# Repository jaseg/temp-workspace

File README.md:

# Speed of the yanartas-sensors sampling front end, with and without the redriver

ngspice simulation of one channel of the sampling front end on the sensing board
(`sensing/yanartas-pillowbox-sensing.kicad_sch` in yanartas-sensors, commit `b0547da`).
Written by an LLM (Claude); nothing in yanartas-sensors was changed.

Two topologies are compared:

- **Redriver as drawn**: FPGA pin → 10 Ω → 220 nF → U2 (PI3HDX12311) → 220 nF → splitter / clip lines.
- **No redriver**: U2 not fitted and each RX pad linked to its TX pad, so the FPGA pin
  drives the splitter and the strobe clip lines itself. Simulated with VCCIO1 at 1.2 V
  (R54, as fitted) and at 3.3 V (the R55 option).

## Result

The speed of the sampler is set by the strobe pulse, and the strobe pulse is set by the
edge that reaches the clip lines. The clip lines are 13.3 mm long (about 160 ps there
and back). An edge slower than that gives a pulse that is as wide as the edge and lower.

| | Sampler 10–90 % rise time (bandwidth) at FPGA edge 150 / 300 / 600 ps | Stimulus 10–90 % at the TDR port |
|---|---|---|
| Redriver, limiting | 134 / 133 / 134 ps (2.6 GHz) | 185 / 228 / 241 ps |
| Redriver, linear | 167 / 236 / 488 ps (2.1 / 1.5 / 0.7 GHz) | 295 / 401 / 689 ps |
| No redriver, 1.2 V | 156 / 283 / 656 ps (2.2 / 1.2 / 0.5 GHz) | 324 / 471 / 819 ps |
| No redriver, 3.3 V | 103 / 82 / 390 ps (at bias +0.93 / +0.53 / +0.20 V per rail) | 326 / 421 / 791 ps |

- **The redriver only makes the front end faster if it limits.** A limiting redriver
  regenerates the edge, so the sampler is about 135 ps whatever the FPGA does. A linear
  redriver passes the FPGA edge on, and the front end is then 10 to 25 % faster than
  without it at 300 to 600 ps FPGA edges and no faster at 150 ps.
- **Which of the two the PI3HDX12311 does on this board is not known.** The part is
  linear for HDMI 2.x and limiting for HDMI 1.4, selected by its straps and its DDC
  listener. I could not obtain the full datasheet (DS46192), so both are simulated.
- **The FPGA edge rate is not known either.** Gowin publishes no slew rate or IBIS data
  for the GW1NZ-1, so it is swept from 150 to 600 ps (20–80 %).
- **Without the redriver at 3.3 V** the strobe pulse is 1.1 to 2.5 V, which allows a
  real reverse bias, so only the tip of the pulse turns the bridge on. That gives the
  fastest sampler of the four cases at FPGA edges up to 300 ps. The stimulus, however,
  would then reach the bridge with 4.3 V differential (the BAT15 is rated 4 V reverse),
  so the stimulus should stay on the redriver. The next section does that.

## Optimised operating point

Free choice of VCCIO1 and of whether the strobe passes through U2; the stimulus stays
on U2. For each option the bridge bias was swept (`sim/optimize.py`,
[all results](results/optimize.md)).

**Recommendation: VCCIO1 at 3.3 V, strobe bypassing U2, bias about +0.45 V per rail**
(VBIAS_K − VBIAS_A ≈ 0.9 V).

| FPGA edge | Operating point | Sampler 10–90 % | Gain | Efficiency | Overshoot |
|---|---|---|---|---|---|
| 150 ps | bypass, 3.3 V, bias +0.55 V | 99 ps | 0.27 | 24 % | 17 % |
| 300 ps | bypass, 3.3 V, bias +0.45 V | 123 ps | 0.25 | 17 % | not recorded |
| 300 ps | bypass, 3.3 V, bias +0.40 V | 152 ps | 0.30 | 23 % | 7 % |
| 600 ps | bypass, 3.3 V, bias +0.30 V | 187 ps | 0.12 | 7 % | 13 % |
| any | through U2 if it limits, bias 0 V | 141–142 ps | 0.15 | 9–10 % | 20–30 % |
| 300 ps | as drawn: through U2 linear, 1.2 V, bias −0.13 V | 236 ps | 0.14 | 16 % | not recorded |

- **Why it is better.** The bias is the speed control: raising it shortens the part of
  the pulse that turns the bridge on, at the price of efficiency. Only a large strobe
  leaves room to do that. Through U2 the pulse is 0.75 V at most and the bridge stops
  working above about 0.1 V of bias.
- **Reverse bias at last.** At +0.45 V per rail the diodes stay off for the ±0.26 V
  that the stimulus puts on the bridge. In the TDR trace the baseline before the edge
  is flat, where the as-drawn case sloped.
- **Recorded TDR edge** (FPGA edge 300 ps): 294 ps incident with U2 linear in the
  stimulus path, against 493 ps as drawn. With U2 limiting the reflected edge is 133 ps.
- **When not to bypass.** At a 600 ps FPGA edge the bypassed strobe needs a low bias and
  is slower than a limiting U2 (187 ps against 141 ps). If the FPGA turns out that slow
  and U2 limits, keep the strobe on U2.
- **VCCIO 2.5 V** is nearly as good (119 ps at +0.30 V and 300 ps, 10 % efficiency) if
  3.3 V is a problem for the other pins of that bank.

What limits the recorded incident edge at this operating point (FPGA edge 300 ps):

| Stimulus path | Edge at the bridge input, 10–90 % | Sampler alone | Limit |
|---|---|---|---|
| U2 linear | 398 ps (409 ps at the FPGA pin) | 122–155 ps | The FPGA edge; U2 passes it on unchanged |
| U2 limiting | 92 ps | 122–155 ps | The sampler for the main rise (about 150 ps in the trace), then a dip 200 ps after the edge |

- The 294 ps read from the trace with U2 linear is shorter than the stimulus itself and
  is not a faithful figure. With the open test line the stimulus rests at ±0.47 V per
  side, as large as the 0.45 V bias, so the bridge compresses the lower end of the edge.
  The ±0.26 V quoted above only holds for a terminated line. For an open or high-impedance
  load the stimulus has to be smaller or the bias larger.
- The sampler slows from 122 ps to 155 ps as the input step grows from 0.05 V to 0.52 V
  per side, and its efficiency falls from 20 % to 11 %.
- The dip with U2 limiting is a reflection from U10, 16.4 mm from the splitter. U10 is
  modelled as 8 Ω with 0.5 pF on each side, which is an estimate, so the size of the dip
  is uncertain. It turns the 10–90 % reading into 345 ps.

Changes on the board:

| Change | Why |
|---|---|
| Fit R55 instead of R54 | VCCIO1 = 3.3 V |
| R78, R79, R82, R83: 10 Ω → about 220 Ω | The stimulus pins now swing 3.3 V; this keeps U2's input near 1.2 V differential. Value not optimised |
| Strobe: connect STROBE_R to STROBE_C through one 220 nF, leaving U2 channels B and D unconnected | Bypass. In the model this is a 1 nH link across the U2 pads; a wire bodge will differ |
| Bias: VBIAS_K ≈ 2.1 V, VBIAS_A ≈ 1.2 V | Tune per board: sweep the bias and take the fastest edge that still has enough amplitude |

Diode reverse voltage at this operating point, simulated over both strobe edges with
the stimulus on an open line (BAT15-04W rating: 4 V): 1.70 V worst case at a 300 ps
FPGA edge, 1.91 V at 150 ps, and 2.17 V at 150 ps with the bias raised to 0.70 V. The
peak falls on the non-sampling strobe edge.

Not checked: the other pins of bank 1 at 3.3 V, the FPGA's drive into the 10 Ω strobe
series resistors at 3.3 V, and R3–R6 (91 Ω), which were left as they are.

In the recorded TDR trace of the four original cases (FPGA edge 300 ps), the incident
edge takes 493 ps with the linear redriver and 541 ps without it at 1.2 V. The
no-redriver 3.3 V trace is left out of that figure. The trace with the limiting redriver is
too noisy to measure, because only 4 % of the error is removed per strobe there.
All numbers are in [results/summary.md](results/summary.md).

## Other things the simulation shows

These apply to both topologies and matter more than the redriver question.

1. **The strobe is barely large enough to turn the bridges on.** With the redriver the
   pulse between the clip-line nodes is 0.2 to 0.75 V, against two diode drops plus
   2 × 91 Ω. To get a 0.65 V forward peak, VBIAS_K − VBIAS_A has to be between +0.1 V
   and −0.4 V, that is, zero or forward bias at idle. The sampling efficiency is then 4
   to 20 % per strobe.
2. **The held voltage is only 0.1 to 0.2 of the input.** Each bridge rail is fed
   through 91 Ω from a clip-line node that is AC-grounded by C73/C74, so the rails are
   not floating. While the bridge conducts, the hold node settles to a divider between
   the signal and the rails.
3. **The stimulus is larger than the bias.** It arrives at the bridge with 0.9 to
   1.4 V differential, so the diodes conduct between strobes. This shows as the sloping
   baseline before the first edge in the TDR trace.

## Method

- `tools/kinet.py` and `tools/pcbpaths.py` read the netlist and the pad-to-pad trace
  lengths from the KiCad files (the files are from a KiCad nightly that no packaged
  `kicad-cli` reads). Their output is in `extracted/`.
- `sim/frontend.py` builds the ngspice deck: both halves of channel 1, traces as LC
  ladders (50 Ω, 6.05 ps/mm), 0402 capacitors with 0.4 nH, the two bridges with their
  91 Ω feeds, hold capacitor and the trace to U13.
- The sampler is measured in equivalent time. For each strobe delay, two transients
  with different starting hold voltages give the voltage a repetitive strobe converges
  to, and the fraction of the error removed per strobe.
- "Sampler rise time" is that held voltage against delay for a 1 ps step driven into
  SPL_HS from 50 Ω. The bias is set per case so that the strobe peaks 0.65 V forward
  across a bridge. With the limiting redriver the response overshoots by 60 % for
  about 300 ps, so its 10–90 % figure flatters it.
- `sim/experiments.py` runs everything (about 40 minutes on 4 cores, ngspice 42),
  `sim/plots.py` makes the figures and the table.

## Assumptions

| Item | Value | Basis |
|---|---|---|
| BAT15-04W | Infineon chip model D315 v7.0, plus 0.7 nH and 0.16 pF per diode | model file; package values from datasheet LS 1.4 nH and C 0.3 pF |
| FPGA output | ramp 150 / 300 / 600 ps into 30 Ω (1.2 V) or 12 Ω (3.3 V), 3 pF | estimate from the DC drive spec; no edge data published |
| PI3HDX12311 | 50 Ω in and out, 9 GHz, 80 ps delay, 1 Vpp differential swing. Linear: 0 dB with 5.6 dB peaking at 6 GHz. Limiting: 20 dB into the same clamp | estimate from the product brief; full datasheet not read |
| Redriver passes single edges at low repetition rate | assumed | not confirmed; a signal-detect or squelch would break this |
| U10 TMUXHS4212 | 8 Ω with 0.5 pF each side | estimate |
| Mesh | ideal 50 Ω line, 1 ns, open | U4/U12, U3/U9, connectors and the mesh itself are not modelled |
| Traces | lossless | |
| Leakage of the hold node between strobes | ignored | |

The estimates decide the absolute numbers. The comparison between the cases depends
mainly on the two unknowns named above.

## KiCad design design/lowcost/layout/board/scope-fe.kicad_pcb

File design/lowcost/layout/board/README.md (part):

# layout/board: scope-fe integrated board (six layers), as built 25 Nov 2026 (BOM-2)

One full run of `python3 gen_board.py` (about 115 s; `--prepower` stops before the supplies, `--powonly` after them; `--fast`
is still broken) builds `scope-fe.kicad_pcb` / `.kicad_pro` / `routes.json`. Renders: `python3 render_board.py` (boardlib `render`, refilled
copy): `scope-fe-L1.png` ... `L6`, `scope-fe-all.png`, `scope-fe-detail-{analog,fpga-south,mcu,power}.png`.

## BOM-2 repair, 25 Nov 2026 (SPEC decision 35, re-check `docs/validation/recheck-bom2.md`)
Full `gen_board.py` run after two block changes; outline, block positions and interfaces unchanged.
- **analog:** R106 is 10 M 0603 now, on B.Cu at (7.50, 15.90) board (block-local 7.50 / 14.90), horizontal. R105.2 ->
  0.3 mm top track (down, 45 degrees west) -> via (6.675, 14.95) -> R106.1; IN_BIAS comes down x 8.52 on B.Cu and jogs
  onto R106.2 (the old IN_BIAS via at x 7.0 is gone). Via hole edge 0.37 mm from the R106 pad; 0.33 mm from R106.2
  to the -5V B track. The top-side 0402 column R105 / (empty) / C107 is unchanged otherwise.
- **phase:** silkscreen within 0.3 mm of the west board edge goes to F.Fab (`silk_fix`): D319's clipped outline.
- **Checks:** check_board 0 missing, extra 4 (H1-H4), 0 footprint / value / pad-net, 0 unrouted, 0 clearance, 0 corner,
  0 off-axis, 0 RF width / gap, 0 courtyard, 0 unconnected (486 footprints, 3475 tracks, 1019 vias); fast-net segments on
  L3 0; 370 L1 / L6 samples without L2 / L5, all antipads or listed windows; L4 +3V3 one polygon; via_in_pad FAIL 0
  (23 near, 31 EP-allowed); DRC jlc4 + parity **0 errors, 0 unconnected, 450 warnings** (the D319 silk_edge_clearance
  is gone); decap_audit 77 capacitors, D1 1, D2s 8, D2g 1, D2p 10 (unchanged). Renders regenerated and looked at
  (L1-L6, all, detail-analog; net views of the R106 area on F and B).
- **Correction (re-check B2-10):** the +2V5 column feed (0.25 mm over 15 mm on L3) carries the trigger selector
  (12.3 mA in signal mode) plus the TLV3801 (up to 26.6 mA), about 40 mA, not "a few mA"; drop about 5 mV, TLV3801
  VCC-GND still >= 2.44 V. Q301 / Q302 emitters are 6-7 mm from the nearest +/-2V5 capacitor (static switch).

## As built 25 Nov 2026 (BOM-2 integration)
All six blocks were regenerated against the BOM-2 netlist, and the board was rebuilt with a full `gen_board.py` run.
The outline is unchanged (100.0 x 57.0 mm), and so are every block position and every interface.

**Front column fix.** The new diode-bridge switch first left the phase column's +2V5 / -2V5 vias unreachable by the
rail router (5 islands failed). Changes (TOPOLOGY.md section 11):
- **TRIG_SEL:** L3 via at (11.3, 23.85), then a 4.3 mm L6 piece to R386. The block's full-height L6 lane is removed.
- **DAC_TRIG:** swaps places with TRIG_SEL in the slow bundle. It is grid-routed east of a fence and enters only
  the column's south end.
- **-2V5:** L6 along x 9.4 (11.2 mm) and an L3 link (4.0 mm).
- **+2V5:** L3 from the Q301 via down the x 9.85 lane (15.9 mm) and to U302's via (10.6 mm). `widen()` grows these
  where room allows.
- **Phase block:** SW_SB now branches south of the U302 +2V5 via (gen_phase.py).

Slow lines: DAC_TRIG 92.5 mm, TRIG_SEL 81.6 mm (incl. the L6 piece 4.3).
Rails: +2V5 is 202 mm on L3 and 33 mm on L6, narrowest 0.25 mm over 15 mm (the explicit column feed, about 40 mA: selector 12.3 mA + TLV3801 up to 26.6 mA, about 5 mV drop).
-2V5 is 206 / 31 mm, narrowest 0.3 mm over 8 mm. The minimum rail-to-signal gap in the column is 0.20 mm, to SW_S;
PH_STROBE is more than 0.3 mm away.

**Checks (25 Nov):**
- **check_board:** 0 missing, extra 4 (H1-H4), 0 footprint / value / pad-net, 0 unrouted, 0 clearance, 0 corner,
  0 off-axis, 0 RF width / gap, 0 courtyard, 0 unconnected (486 footprints, 3467 tracks, 1018 vias).
- **gen_board:** fast-net segments on L3 0; 370 L1 / L6 samples without L2 / L5, all antipads or listed windows
  (0 real holes); L4 +3V3 is one polygon.
- **via_in_pad:** FAIL 0 (23 near, 31 in listed exposed pads).
- **DRC jlc4 + parity:** 451 warnings, 0 errors, 0 unconnected.
  - New since 24 Nov: 1 silk_edge_clearance (D319 silk at the west edge, x 0.25).
  - Otherwise as before: field / library mismatches, 31 attribute (5 DNP: C631, D402, D403, D601, R122),
    10 net_conflict.
- **decap_audit:** 77 capacitors; D1 1, D2s 8, D2g 1 (was 3; C301 / C306 are gone), D2p 10.
- **GND stitching:** 44 of 81 fast vias have a GND via within 1 mm.

**Not redone:** the block `*_netview_*.png` crops (they show the 24 Nov board) and `phase_netview_u301.png`
(U301 no longer exists).

## As built (24 Nov 2026, new power tree)
Board 100.0 x 57.0 mm (unchanged), JLC06161H-3313: L1 RF / parts, L2 GND, L3 slow lines + minor rails, L4 +3V3, L5 GND, L6 buses.
Flow: merge blocks -> L1 / L6 signal routes -> planes -> slow lines (`board_slow.py`, explicit) -> block clean-up ->
supplies (`board_power.py`) -> widen -> GND stitching -> silk -> fill -> rule-10 check -> check_board.

**Supplies** (`board_power.py`, rewritten): L4 is one +3V3 plane (one polygon) plus the FPGA block's +1V2 island, joined to
the U602 output via (75.0, 7.9) by an L4 finger along the power block's west edge (x 73.2-75.65, y 7.35-15.2). Every other
rail is a set of TRACKS from its regulator via: a 0.1 mm grid router (L3, L6 at 3x cost + via cost) joins each copper island
of the rail to the tree at the widest width that fits (rail widths 1.2 / 0.8 mm first), keeping 0.18 mm to other copper
(Power netclass 0.15), 0.3 mm to slow lines, 0.5 mm to ADC_IN, a soft 0.6 mm keep-off around L3 cut-outs (node windows);
`widen()` then fattens each segment to the widest that fits (<= 1.5 mm +5V1, 1.0 mm others). Router copper only (block
copper excluded):

| rail | load | L3 mm | L6 mm | >= 0.5 mm | narrowest stretch |
|---|---|---|---|---|---|
| /+5V1 (GVA-84+ chokes) | 0.34 A | 86.5 | 5.8 | 100 % | 0.6 mm, 6.3 mm in total (choke joins in pstrobe, about 0.17 A each); trunk 0.8-1.5 mm |
| +5V | 41 mA | 125.8 | 0 | 100 % | 0.6 mm, 6.4 mm (x 12, y 10-16, BUF802 area) |
| -5V | 41 mA | 74.4 | 7.3 | 100 % | 0.6 mm, 57 mm (x 17-70, y 13-17) |
| +2V5 | 50 mA | 269.1 | 10.5 | 91 % | **0.3 mm, 26 mm** (x 10-12, y 26-49: the branch to U301 / C301 / C306 through the trigger front end, < 1 mA) |
| -2V5 | 50 mA | 204.6 | 24.6 | 100 % | 0.4 mm, 1.0 mm |
| VBUS (J501 pin 1 only) | programmer | 85.3 | 9.5 | 100 % | 0.6 mm, 85 mm |
| /VTAP_P, /VTAP_N | 12.5 mA | 78 / 119 | 21 / 43 | 95 / 100 % | 0.4 mm 4.9 mm / 0.6 mm |
IPC-2221 (10 K, inner 0.5 oz): 0.3 mm 0.27 A, 0.6 mm 0.45 A, 1.0 mm 0.65 A. Regulator input headroom: blocks/power/README.md.

**Slow lines** (`board_slow.py`, TOPOLOGY.md section 9 geometry, drawn before the supplies): all 9 routed (ADC_REF_MID
56.6, DAC_TRIG 90.0, VOFS 82.6, VBIAS_A 77.5, VBIAS_K 73.0, VTAP_TH 23.7, TRIG_SEL 104.5, ADC_IN 77.3, VNEG_REF 58.9 mm).
VBIAS_A's analog via moved to (15.4, 15.9) (the analog block's BUF_OUT_T moved).

**Validation items done at board level**
- PDN-2 type: U601 (0.30 W, hottest) GND polygon with 6 vias at the capacitor GND pads (TIGHTEN), shared with U602 (B).
- ZONES-3: L2 / L5 GND clearance 0.15 mm, min width 0.15 mm; fpga east-pin vias and TAP8-15 via rows staggered to
  >= 1.0 mm (blocks/fpga/README.md). Not feasible: the COARSE / TAP0-4 via stair (0.57 mm pitch) and the mcuif row.
- ZONES-4: GND via within 1 mm of 42 of 82 fast-net vias (validation: 22 of 72), incl. both S_STROBE_N vias (0.65 mm).
  The other 40 sit in the dense fpga fan-out, the TAP output vias and the mcuif row; no free spot within 1 mm there.
- DECOUPLING-5 / -6 (fpga block; C502 / C506 still share one GND via), DECOUPLING-8 (C602 moved to U608 pin 5), U603 /
  L601 compacted (switch nodes 1.9 mm).
- IO-3: not done (the schematic did not move CLK2 off pin 34).
- TIGHTEN (24 Nov, user review of the power render): decoupling capacitors at their pins, plane vias at the capacitors.
  U603: C601 / C610 courtyards on the chip's (0.0 mm), VBUS / +5V1 pad 0.93 mm from VIN / VOUT (was 2.0), GND pads
  returned to PGND on L1 through the channel between the pin columns; input / output hot loop 3.1 x 3.9 -> 1.9 x 2.8 mm
  (11.2 -> 2.8 mm2, now without plane vias in the loop); vias only behind the capacitors (none at the pins / under L601).
  U601 / U602: COUT under CIN (output loop 4.35 x 4.05 -> 4.0 x 2.7 mm), vias moved from the middle of the GND polygon to
  the capacitor pads, +3V3 vias behind C604 / C609. LM27762: GND vias at the CIN GND pads. Elsewhere (audit
  `decap_audit.py` over this board): analog U101 -5V rail via between pins 5 / 6 removed (via-only rule area over the pin
  row; the rail now lands on the vias behind C112), phase U310 C351 and mcuif C716 GND vias at the pads. At TIGHTEN every
  primary capacitor passed D1 / D2s / D2g except C621 (then on B; on F since REPAIR); the 9 remaining flags were bulk /
  second capacitors placed off the pins by design (C507, C510, C616, C505 / C506, C711, C714, C306, C717).
  Audit of the current board (after REPAIR, with the per-pin class D2p): 78 capacitors, D1 1 (U101.6 / C116 on B: pins
  5 / 6 share C112 on top), D2s 8, D2g 3, D2p 10; the D2p / D2s cases at the primary capacitors are the ones listed under
  REPAIR (RF2-3) plus U501.25 / .36 (C505 / C506) and U502.1 (C509), see docs/VALIDATION.md.
  Review renders: `net_view.py` (net-coloured copper, vias, courtyards), e.g. blocks/power/power_netview_*.png.

**REPAIR (24 Nov, independent re-check docs/validation/recheck-*.md)**
- RP-1: LM27762 output capacitors C617 / C621 / C630 / C628 moved from B to the IC layer at OUT+ / OUT- (no vias between
  pin and capacitor, rail vias behind them); dividers rearranged (blocks/power/README.md). +5V / -5V sources moved to
  (82.05, 7.0) / (74.4, 13.6).
- RF2-1: U301 pin 10 (+2V5) fed through a 0.4 mm via beside pin 9 and a B track to C301 / C306: no +2V5 copper or via
  beside BUF_OUT_T any more (was 0.105 mm via edge), L2 solid under the trace.
- RF2-5: TAP5 via 0.15 mm east, 0.4 mm: its antipad stays 0.03 mm clear of PH_STROBE_N's edge (L2 solid under it).
- RF2-3 (vias at the IC pins): U704 pin 24 via now north of C712; U502 pin-1 end of the VDDO link lands at C623;
  U101 pin 8 polygon starts at C113 (vias east of C113, not at the pin end). `decap_audit.py` has a new class D2p
  (via nearer the pin than any capacitor pad of the net, per pin). Remaining D2p, kept: U101.1 / .12 and U501.1 (vias
  join a polygon / tracks that end in the capacitor pad: cap first in the copper path), U704.36 (R727 I2C pull-up feed,
  not a decoupling via), U704.48 / .1 (inner via is C710's (B) via; no room behind C713: bus track north, pins east /
  south), U502.7 (C508 boxed in by the CLK2 track), U310.8 (the L6 fan-in west of C351), U604.3 (EN+ tie via); U201.5 (not in the re-check list, not examined).
- board_power.widen(): exact distance check to foreign vias / tracks (raster missed a /+5V1 interface via), shrinks a
  rail segment that would violate the netclass gap (+2V5 0.8 -> 0.6 mm at (87.1, 20.3); /+5V1 0.5 -> 0.4 mm at two
  pstrobe choke joins).
- RF2-6: the rail router keeps 0.15 mm extra from fast / clock / strobe / comparator nets (rail edge >= 0.33 mm on
  L3 / L6; the VTAP_N / MCU_CLK, +2V5 / PH_STROBE_N and VTAP_N / U310A+ cases are gone). Left: block pin necks at the
  FPGA (+3V3 / TAP8 0.155 mm, +1V2 / S_STROBE_P and +3V3 / S_STROBE_N 0.22 mm, set by the 0.5 mm pin pitch).
- RF2-9: schematic DNP parts (C631, D402, D403, R122) are excluded from the pos file by gen_board.
- floorplan.PLACED_IN: C606 / C614 / C616 / C622 / C402-C409 -> analog, C615 / C620 / J102 / R122 -> phase, J501 / R511 /
  R512 -> mcuif.
- RF2-4: superseded by 'Vias out of pads' below (no plugged vias are ordered).
- Net-view crops: blocks/power/power_netview_lm27762*.png, blocks/phase/phase_netview_u301.png,
  blocks/analog/analog_netview_u101.png, blocks/mcuif/mcuif_netview_u704.png, blocks/fpga/fpga_netview_{u502,tap5}.png.

**Vias out of pads (24 Nov, user decision: no plugged / capped / filled vias; RULES.md rule 12)**
Standard JLCPCB six-layer order, ordinary tented vias. `via_in_pad.py` (run by gen_board.py, also per block) lists every
via whose hole is < 0.15 mm from a soldered SMD pad (copper, mask or paste opening; JP solder jumpers count as soldered)
or whose ring reaches into a mask opening: board FAIL 0 (was 88 pad hits), 30 legal at 0.15-0.2 mm. Fixed in the
generators: pstrobe (C413 / C423 10 uF re-placed off the 0402 GND vias, their +3V3 via pairs moved north; C430 / C420 bulk
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
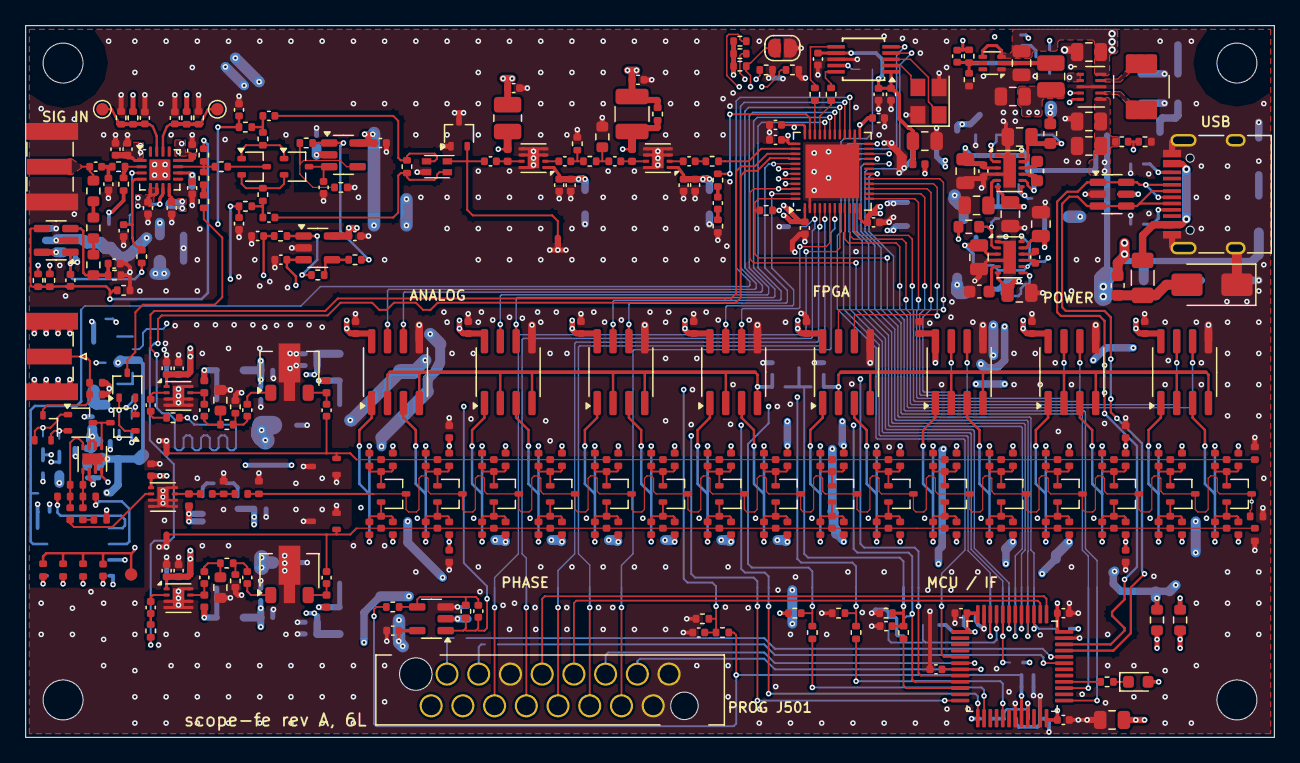
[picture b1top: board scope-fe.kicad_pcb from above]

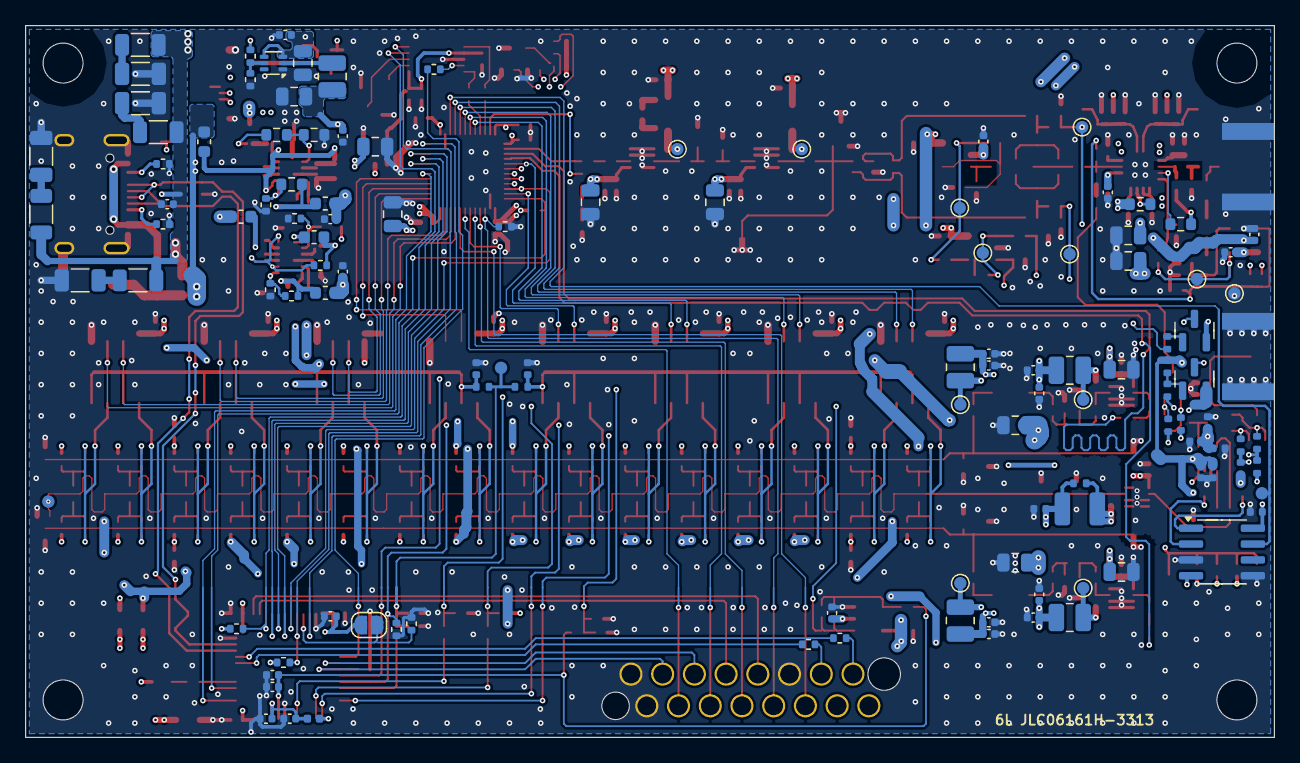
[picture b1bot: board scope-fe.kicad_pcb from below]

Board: 6 copper layers, 100.0 x 57.0 mm, 486 parts (118 on the bottom side), 254 nets.

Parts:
C101: 1.5p; C_0402_1005Metric
C102: 3.3p; C_0402_1005Metric
C103, C104, C308, C311, C312, C356, C358, C607, C608, C615, C623, C624, C627, C715, C717: 1u; C_0402_1005Metric
C105: 18p; C_0402_1005Metric
C106, C404, C409, C415, C418, C425, C428: 1n; C_0402_1005Metric
C107, C207, C631: 100p; C_0402_1005Metric
C108, C109, C110, C112, C113, C114, C115, C208, C209, C210, C305, C306, C307, C309, C310, C313, C346, C347, C348, C349, C350, C351, C352, C353, C354, C355, C357, C359, C401, C403, C405, C406, C408, C410, C411, C412, C414, C416, C417, C419, C421, C422, C424, C426, C427, C429, C431, C432, C433, C434, C435, C501, C502, C504, C505, C506, C508, C509, C602, C606, C613, C622, C629, C709, C710, C711, C712, C713, C718, C719, C720, C721, C722: 100n; C_0402_1005Metric
C111, C116, C402, C407, C413, C420, C423, C430, C503, C507, C510, C603, C609, C617, C621, C625, C626, C628, C630, C714: 10u; C_0805_2012Metric
C201, C202: 47p; C_0402_1005Metric
C203, C204, C206, C304, C614, C702, C716: 10n; C_0402_1005Metric
C205: 2.2p; C_0402_1005Metric
C314, C315, C316, C317, C318, C319, C320, C321, C322, C323, C324, C325, C326, C327, C328, C329, C330, C331, C332, C333, C334, C335, C336, C337, C338, C339, C340, C341, C342, C343, C344, C345: 0.5p; C_0402_1005Metric
C601, C604, C605, C610, C611, C612: 22u; C_0805_2012Metric
C616, C620: 4.7u; C_0402_1005Metric
C618: 1u; C_0603_1608Metric
C619: 4.7u; C_0603_1608Metric
C632, C633, C634, C635: 47u; C_1206_3216Metric
D201, D202, D301, D302, D303, D304, D305, D306, D307, D308, D309, D310, D311, D312, D313, D314, D315, D316, D317, D318, D319, D320, D401, D402, D403: BAT15-04W; SOT-323_SC-70
D601: SMAJ5.0A; D_SMA
D701: red; LED_0603_1608Metric
F601: 0; Fuse_1206_3216Metric
FB301, FB401, FB402, FB403, FB404, FB405, FB406, FB608, FB701: 1k; L_0402_1005Metric
FB601, FB602, FB603, FB604, FB605, FB606, FB607: 120R@100MHz; L_0603_1608Metric
H1, H2, H3, H4: MountingHole_3.2mm_M3
J101: SIG_IN; SMA_Samtec_SMA-J-P-X-ST-EM1_EdgeMount
J102: EXT_CLK; SMA_Samtec_SMA-J-P-X-ST-EM1_EdgeMount
J501: WR-WST 490107671612; Würth_WR-WST_debug_490107671612_2x08_P2.54mm_Vertical
J601: USB-C 16P; USB_C_Receptacle_HRO_TYPE-C-31-M-12
JP501: JTAGSEL; SolderJumper-2_P1.3mm_Open_RoundedPad1.0x1.5mm
JP701: BOOT0; SolderJumper-2_P1.3mm_Open_RoundedPad1.0x1.5mm
L302, L401: 47u; L_1210_3225Metric
L402, L403, L404, L405, L406, L602, L603: 1u; L_1008_2520Metric
L601: 0.47u; L_XR0420_4.4x4.2mm
NT401, NT402, NT403: stub short; NetTie-2_SMD_Pad0.5mm
Q301: SS8550; SOT-23
Q302: MMBT3904; SOT-23
R104, R201: 10; R_0402_1005Metric
R105: 1M; R_0402_1005Metric
R106: 10M; R_0603_1608Metric
R107: 18k; R_0603_1608Metric
R108, R110, R121, R204, R205, R206, R209, R210, R315, R316, R319, R320, R323, R324, R327, R328, R331, R332, R335, R336, R339, R340, R343, R344, R347, R348, R351, R352, R355, R356, R359, R360, R363, R364, R367, R368, R371, R372, R375, R376, R380, R381, R382, R387, R390, R391, R392, R393, R394, R415, R724, R730: 1k; R_0402_1005Metric
R109, R111: 1.5k; R_0402_1005Metric
R112, R122, R301, R310, R377, R378, R379, R401, R405, R406, R407, R411: 49.9; R_0402_1005Metric
R113: 0; R_0402_1005Metric
R114, R115, R116: 300k; R_0603_1608Metric
R117, R607, R608, R609, R611, R612, R617: 100k; R_0402_1005Metric
R118, R501, R502, R503, R504, R505, R506, R507, R727, R728, R735: 4.7k; R_0402_1005Metric
R119, R384, R386, R388, R703, R729, R732: 10k; R_0402_1005Metric
R120, R610: 22k; R_0402_1005Metric
R123, R731: 15k; R_0402_1005Metric
R202, R203: 22; R_0402_1005Metric
R207: 1.00k; R_0402_1005Metric
R208: 510; R_0402_1005Metric
R211, R508, R509, R510: 33; R_0402_1005Metric
R306, R307, R308, R309, R403, R410, R414, R511, R512: 100; R_0402_1005Metric
R311, R312: 470; R_0402_1005Metric
R313, R314, R317, R318, R321, R322, R325, R326, R329, R330, R333, R334, R337, R338, R341, R342, R345, R346, R349, R350, R353, R354, R357, R358, R361, R362, R365, R366, R369, R370, R373, R374, R604: 2.2k; R_0402_1005Metric
R383, R601, R602, R733, R736: 5.1k; R_0402_1005Metric
R385, R389, R704, R734, R737: 3.3k; R_0402_1005Metric
R402: 100; R_0603_1608Metric
R404, R409, R413: 120; R_0402_1005Metric
R408, R412: 120; R_0603_1608Metric
R603: 20k; R_0402_1005Metric
R605: 510k; R_0603_1608Metric
R606, R616: 200k; R_0402_1005Metric
R613: 470k; R_0603_1608Metric
R614: 150k; R_0603_1608Metric
R615: 220k; R_0603_1608Metric
R618, R619, R620, R621: 1; R_1206_3216Metric
R723: 33k; R_0402_1005Metric
R725, R726: 0; R_0603_1608Metric
T401: DLW21SN900HQ2L; L_CommonModeChoke_Coilcraft_0805USB
TL401: Z0=50 TD=80p; TLine_TL401
TL402: Z0=50 TD=80p; TLine_TL402
TL403: Z0=50 TD=80p; TLine_TL403
TP101: CLH; TestPoint_Pad_D1.0mm
TP102: CLL; TestPoint_Pad_D1.0mm
TP103: SERVO; TestPoint_Pad_D1.0mm
TP104: GND; TestPoint_Pad_D1.0mm
TP201: VBIAS_A; TestPoint_Pad_D1.0mm
TP202: VBIAS_K; TestPoint_Pad_D1.0mm
TP203: HOLD_OUT; TestPoint_Pad_D1.0mm
TP204: SHIFT_OUT; TestPoint_Pad_D1.0mm
TP302: TRIG_LEVEL; TestPoint_Pad_D1.0mm
TP303: COARSE; TestPoint_Pad_D1.0mm
TP304: LINE_IN; TestPoint_Pad_D1.0mm
TP305: VTAP_TH; TestPoint_Pad_D1.0mm
TP401: TRF1_OUT; TestPoint_Pad_D1.0mm
TP402: TRF2_OUT; TestPoint_Pad_D1.0mm
TP403: PTRF1_OUT; TestPoint_Pad_D1.0mm
TP404: GVA1_VD; TestPoint_Pad_D1.0mm
TP405: PTRF2_OUT; TestPoint_Pad_D1.0mm
TP406: GVA2_VD; TestPoint_Pad_D1.0mm
U101: BUF802IRGTR; VQFN-16-1EP_3x3mm_P0.5mm_EP1.68x1.68mm
U102: OPA197IDBVR; SOT-23-5
U201, U202, U701: TPH2501; SOT-23-5
U302: TLV3801; WSON-8-1EP_2x2mm_P0.5mm_EP0.9x1.6mm
U303, U401, U402, U403, U405: TRF37D73; WSON-8-1EP_2x2mm_P0.5mm_EP0.9x1.6mm
U305, U306, U307, U308, U309, U310, U311, U312, U313: COS3502; SOIC-8_3.9x4.9mm_P1.27mm
U404, U406: GVA-84+; SOT-89-3
U501: GW1NZ-LV1QN48C6/I5; QFN-48-1EP_6x6mm_P0.4mm_EP4.3x4.3mm
U502: MS5351M; MSOP-10_3x3mm_P0.5mm
U601, U602: TPS62A01ADRLR; SOT-563
U603: TPS63802DLAR; Texas_DLA0010A_VSON-HR-10_2x3mm_P0.5mm
U604, U605: LM27762DSSR; WSON-12-1EP_3x2mm_P0.5mm_EP1x2.65
U608: USBLC6-2SC6; SOT-23-6
U704: STM32G474CBT6; LQFP-48_7x7mm_P0.5mm
Y501: 25MHz; Crystal_SMD_3225-4Pin_3.2x2.5mm

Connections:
+1V2: C501.1, C502.1, C503.1, C605.1, C608.1, L603.2, R611.1, U501.12, U501.37
+2V5: C208.1, C305.2, C306.2, C615.1, C720.1, FB606.2, Q301.2, R108.1, R390.1, R725.1, U201.5, U302.6, U302.7, U701.5
+3V3: C210.1, C309.2, C310.2, C313.2, C346.1, C347.1, C348.1, C349.1, C350.1, C351.1, C352.1, C353.1, C402.1, C403.1, C404.1, C407.1, C408.1, C409.1, C413.1, C414.1, C415.1, C423.1, C424.1, C425.1, C432.1, C433.1, C434.1, C435.1, C504.1, C505.1, C506.1, C507.1, C604.1, C606.1, C607.1, C609.1, C622.1, C631.1, C710.1, C711.1, C712.1, C713.1, C714.1, D701.2, FB605.1, FB608.1, FB701.1, J501.3, JP701.2, L302.1, L401.2, L402.2, L403.2, L405.2, L602.2, R382.1, R415.2, R501.1, R502.1, R503.1, R504.1, R609.1, R727.1, R728.1, U202.5, U303.1, U305.8, U306.8, U307.8, U308.8, U309.8, U310.8, U311.8, U312.8, U313.4, U313.8, U401.1, U402.1, U403.1, U405.1, U501.1, U501.25, U501.36, U602.3, U602.4, U704.1, U704.24, U704.36, U704.48
+5V: C108.1, C109.1, C110.1, C111.1, C616.1, FB604.2, U101.1, U101.12, U102.5
-2V5: C209.2, C307.1, C620.1, C629.1, C721.2, FB607.2, Q302.2, R110.2, R384.2, R387.2, R389.2, R726.1, R734.2, U201.2, U302.3, U302.9, U701.2
-5V: C112.1, C113.1, C114.1, C115.1, C116.1, C614.1, C627.1, FB603.2, R107.2, U101.5, U101.6, U101.8, U101.10, U102.2
/+5V1: C418.1, C419.1, C420.1, C428.1, C429.1, C430.1, C610.1, C611.1, FB602.1, L404.2, L406.2, R603.1, U603.6
/ADC_IN: C207.1, R211.2, U704.8
/ADC_REF_MID: C206.1, C702.1, R703.2, R704.1, U202.3
/ADC_TRIG: U501.18, U704.25
/BUF_OUT_S: R112.1, R118.2, R201.1, U101.11
/BUF_OUT_T: D317.3, R113.2
/COARSE: TP303.1, U313.7, U501.27
/DAC_TRIG: R383.2, U704.12
/DBG1: J501.12, U704.6
/EXT_CLK: D319.3, J102.1, R122.1, R301.1
/FPGA_DONE: R502.2, U501.46, U704.43
/FPGA_RECONFIG: R501.2, U501.48, U704.27
/HOST_RX: R511.2, U704.32
/HOST_TX: R512.2, U704.31
/I2C_SCL: R727.2, U502.4, U704.39
/I2C_SDA: R728.2, U502.5, U704.44
/MCU_CLK: R509.2, U704.5
/PH_STROBE_N: R411.1, U501.40
/PH_STROBE_P: R407.1, U501.39
/PSTRB_A: C314.1, C316.1, C318.1, C320.1, C322.1, C324.1, C326.1, C328.1, C330.1, C332.1, C334.1, C336.1, C338.1, C340.1, C342.1, C344.1, C421.2, D402.2, R379.1, TL402.1
/PSTRB_K: C315.1, C317.1, C319.1, C321.1, C323.1, C325.1, C327.1, C329.1, C331.1, C333.1, C335.1, C337.1, C339.1, C341.1, C343.1, C345.1, C431.2, D403.1, R378.1, TL403.1
/SPI_CS: U501.24, U704.46
/SPI_MISO: U501.21, U704.41
/SPI_MOSI: U501.22, U704.42
/SPI_SCK: U501.20, U704.40
/STRB_A: C201.1, R204.1, T401.2
/STRB_K: C202.1, R204.2, T401.4
/S_STROBE_N: R405.1, U501.35
/S_STROBE_P: R401.1, U501.38
/TAP0: U305.7, U501.28
/TAP1: U305.6, U501.29
/TAP2: U306.7, U501.30
/TAP3: U306.6, U501.31
/TAP4: U307.7, U501.32
/TAP5: U307.6, U501.41
/TAP6: U308.7, U501.47
/TAP7: U308.6, U501.6
/TAP8: U309.7, U501.17
/TAP9: U309.6, U501.16
/TAP10: U310.7, U501.15
/TAP11: U310.6, U501.14
/TAP12: U311.7, U501.13
/TAP13: U311.6, U501.11
/TAP14: U312.7, U501.10
/TAP15: U312.6, U501.9
/TRIG_SEL: R386.1, R737.1, U704.9
/UC_NRST: C719.1, J501.14, U704.7
/UC_SWCLK: J501.10, U704.38
/UC_SWDIO: J501.8, U704.37
/USB_DM: J601.A7, J601.B7, U608.3, U608.4, U704.33
/USB_DP: J601.A6, J601.B6, U608.1, U608.6, U704.34
/VBIAS_A: C203.1, R205.1, R733.2, R734.1, TP201.1
/VBIAS_K: C204.1, R206.2, R735.2, R736.1, TP202.1
/VNEG_REF: C722.2, R123.1, R732.2, U701.1
/VOFS: R119.1, U704.13
/VTAP_N: C358.1, C359.1, R313.2, R317.2, R321.2, R325.2, R329.2, R333.2, R337.2, R341.2, R345.2, R349.2, R353.2, R357.2, R361.2, R365.2, R369.2, R373.2, R726.2
/VTAP_P: C356.1, C357.1, R314.2, R318.2, R322.2, R326.2, R330.2, R334.2, R338.2, R342.2, R346.2, R350.2, R354.2, R358.2, R362.2, R366.2, R370.2, R374.2, R725.2
/VTAP_TH: C709.1, R380.1, R381.1, R723.2, R724.1, TP305.1
/fpga_clock/+3V3_CLK: C508.1, C509.1, C510.1, C623.1, FB608.2, U502.1, U502.7
/fpga_clock/CLK2_FPGA: R510.2, U501.34
/fpga_clock/DBG2: J501.5, U501.8
/fpga_clock/FPGA_CLK: R508.2, U501.33
/fpga_clock/FPGA_MODE0: R505.1, U501.43
/fpga_clock/FPGA_MODE1: R506.1, U501.42
/fpga_clock/FPGA_READY: R503.2, U501.45
/fpga_clock/JTAGSEL_N: JP501.1, R504.2, U501.44
/fpga_clock/JTAG_TCK: J501.7, R507.1, U501.3
/fpga_clock/JTAG_TDI: J501.11, U501.5
/fpga_clock/JTAG_TDO: J501.13, U501.7
/fpga_clock/JTAG_TMS: J501.9, U501.4
/input/FB: C106.1, R118.1, R119.2, R120.1, R123.2, U102.4
/input/GA: C101.2, C102.1, R104.1
/input/IN_AUX: C107.1, R121.2, U101.4
/input/TAP: C105.1, R116.2, R117.1, U102.3
/input/VIN: C101.1, J101.1, R114.1
/mcu_if/BOOT0: JP701.1, R729.1, U704.45
/mcu_if/DAC_BIAS_A: R733.1, U704.14
/mcu_if/DAC_BIAS_K: R735.1, U704.17
/mcu_if/DAC_TAPTH: R723.1, U704.10
/mcu_if/LED: R730.2, U704.28
/mcu_if/VDDA: C715.1, C716.1, FB701.2, U704.21
/mcu_if/VREFP: C717.1, C718.1, R703.1, R731.1, U704.20
/power/+2V5_LDO: C630.1, FB606.1, R615.2, U605.11
/power/+3V3_CP: C625.1, FB605.2, R617.1, U605.3
/power/+5V1F: C612.1, C613.1, FB602.2, U604.3, U604.8, U604.12
/power/+5V_LDO: C617.1, FB604.1, R613.2, U604.11
/power/-2V5_LDO: C628.1, FB607.1, R607.1, U605.6
/power/-5V_LDO: C621.1, FB603.1, R605.1, U604.6
/power/CC1: J601.A5, R601.1
/power/CC2: J601.B5, R602.1
/power/PG_5V1: R617.2, U603.5, U605.8, U605.12
/power/VBUS_F: D601.2, F601.2, FB601.1
/power/VBUS_IN: F601.1, J601.A4, J601.A9, J601.B4, J601.B9
/trigger_phase/CMP_N: C312.1, R306.2, R312.1, U302.1
/trigger_phase/CMP_P: C308.1, R306.1, R311.1, U302.8
/trigger_phase/SW_S: Q301.3, R387.1, R388.1, R391.1, R394.2
/trigger_phase/SW_SB: Q302.3, R390.2, R392.2, R393.1
/trigger_phase/TRIG_IN: D318.3, D320.3, U302.5
/trigger_phase/TRIG_LEVEL: C304.1, R383.1, R384.1, R385.1, TP302.1, U302.4
/trigger_phase/VTH1: C354.1, R380.2, U305.2, U305.4, U306.2, U306.4, U307.2, U307.4, U308.2, U308.4
/trigger_phase/VTH2: C355.1, R381.2, U309.2, U309.4, U310.2, U310.4, U311.2, U311.4, U312.2, U312.4
GND: C102.2, C103.2, C104.2, C105.2, C107.2, C108.2, C109.2, C110.2, C111.2, C112.2, C113.2, C114.2, C115.2, C116.2, C203.2, C204.2, C205.2, C206.2, C207.2, C208.2, C209.1, C210.2, C304.2, C305.1, C306.1, C307.2, C309.1, C310.1, C313.1, C346.2, C347.2, C348.2, C349.2, C350.2, C351.2, C352.2, C353.2, C354.2, C355.2, C356.2, C357.2, C358.2, C359.2, C402.2, C403.2, C404.2, C407.2, C408.2, C409.2, C413.2, C414.2, C415.2, C418.2, C419.2, C420.2, C423.2, C424.2, C425.2, C428.2, C429.2, C430.2, C432.2, C433.2, C434.2, C435.2, C501.2, C502.2, C503.2, C504.2, C505.2, C506.2, C507.2, C508.2, C509.2, C510.2, C601.2, C602.2, C603.2, C604.2, C605.2, C606.2, C607.2, C608.2, C609.2, C610.2, C611.2, C612.2, C613.2, C614.2, C615.2, C616.2, C617.2, C619.2, C620.2, C621.2, C622.2, C623.2, C625.2, C626.2, C627.2, C628.2, C629.2, C630.2, C632.2, C633.2, C634.2, C635.2, C702.2, C709.2, C710.2, C711.2, C712.2, C713.2, C714.2, C715.2, C716.2, C717.2, C718.2, C719.2, C720.2, C721.1, D401.1, D401.3, D402.1, D402.3, D403.2, D403.3, D601.1, J101.2, J102.2, J501.6, J501.15, J501.16, J601.A1, J601.A12, J601.B1, J601.B12, J601.S1, JP501.2, NT401.2, NT402.2, NT403.2, R109.2, R111.2, R117.2, R120.2, R122.2, R208.2, R301.2, R307.2, R309.2, R310.2, R377.2, R378.2, R379.2, R385.2, R402.2, R403.2, R406.2, R408.2, R409.2, R412.2, R413.2, R505.2, R506.2, R507.2, R601.2, R602.2, R604.2, R606.2, R608.2, R610.2, R612.2, R614.1, R616.1, R704.2, R724.2, R729.2, R736.2, R737.2, T401.3, TP104.1, U101.17, U202.2, U302.2, U303.3, U303.4, U303.5, U303.6, U303.8, U303.9, U305.5, U306.5, U307.5, U308.5, U309.5, U310.5, U311.5, U312.5, U313.3, U313.5, U401.3, U401.4, U401.5, U401.6, U401.8, U401.9, U402.3, U402.4, U402.5, U402.6, U402.8, U402.9, U403.3, U403.4, U403.5, U403.6, U403.8, U403.9, U404.2, U405.3, U405.4, U405.5, U405.6, U405.8, U405.9, U406.2, U501.2, U501.26, U501.49, U502.8, U601.1, U602.1, U603.3, U603.8, U604.1, U604.4, U604.13, U605.1, U605.4, U605.13, U608.2, U701.3, U704.19, U704.23, U704.35, U704.47, Y501.2, Y501.4
unnamed: C106.2, R121.1, TP103.1, U102.1
unnamed: C201.2, R202.1, R205.2
unnamed: C202.2, R203.2, R206.1
unnamed: C311.2, R307.1, R308.1
unnamed: C312.2, R310.1
unnamed: C401.1, R401.2
unnamed: C405.2, R402.1, R404.1
unnamed: C406.1, R403.1, R404.2
unnamed: C411.1, R405.2
unnamed: C411.2, R406.1
unnamed: C412.1, R407.2
unnamed: C416.2, R408.1, R410.1
unnamed: C417.1, R409.1, R410.2
unnamed: C422.1, R411.2
unnamed: C426.2, R412.1, R414.1
unnamed: C427.1, R413.1, R414.2
unnamed: C632.1, R618.2
unnamed: C633.1, R619.2
unnamed: C634.1, R620.2
unnamed: C635.1, R621.2
unnamed: D201.1, D202.1, R202.2
unnamed: D201.2, D202.2, R203.1
unnamed: D201.3, R201.2
unnamed: C205.1, D202.3, U201.3
unnamed: C314.2, D301.1, R313.1, R315.1
unnamed: C315.2, D301.2, R314.1, R316.1
unnamed: D301.3, D302.3, D303.3, D304.3, D305.3, D306.3, D307.3, D308.3, D309.3, D310.3, D311.3, D312.3, D313.3, D314.3, D315.3, D316.3, R308.2, R309.1, R377.1, TP304.1
unnamed: C316.2, D302.1, R317.1, R319.1
unnamed: C317.2, D302.2, R318.1, R320.1
unnamed: C318.2, D303.1, R321.1, R323.1
unnamed: C319.2, D303.2, R322.1, R324.1
unnamed: C320.2, D304.1, R325.1, R327.1
unnamed: C321.2, D304.2, R326.1, R328.1
unnamed: C322.2, D305.1, R329.1, R331.1
unnamed: C323.2, D305.2, R330.1, R332.1
unnamed: C324.2, D306.1, R333.1, R335.1
unnamed: C325.2, D306.2, R334.1, R336.1
unnamed: C326.2, D307.1, R337.1, R339.1
unnamed: C327.2, D307.2, R338.1, R340.1
unnamed: C328.2, D308.1, R341.1, R343.1
unnamed: C329.2, D308.2, R342.1, R344.1
unnamed: C330.2, D309.1, R345.1, R347.1
unnamed: C331.2, D309.2, R346.1, R348.1
unnamed: C332.2, D310.1, R349.1, R351.1
unnamed: C333.2, D310.2, R350.1, R352.1
unnamed: C334.2, D311.1, R353.1, R355.1
unnamed: C335.2, D311.2, R354.1, R356.1
unnamed: C336.2, D312.1, R357.1, R359.1
unnamed: C337.2, D312.2, R358.1, R360.1
unnamed: C338.2, D313.1, R361.1, R363.1
unnamed: C339.2, D313.2, R362.1, R364.1
unnamed: C340.2, D314.1, R365.1, R367.1
unnamed: C341.2, D314.2, R366.1, R368.1
unnamed: C342.2, D315.1, R369.1, R371.1
unnamed: C343.2, D315.2, R370.1, R372.1
unnamed: C344.2, D316.1, R373.1, R375.1
unnamed: C345.2, D316.2, R374.1, R376.1
unnamed: D317.1, D318.1, R391.2
unnamed: D317.2, D318.2, R392.1
unnamed: D319.1, D320.1, R393.2
unnamed: D319.2, D320.2, R394.1
unnamed: C410.2, D401.2, T401.1, TL401.1
unnamed: D701.1, R730.1
unnamed: FB301.2, L302.2, R382.2
unnamed: FB401.2, L401.1, R415.1, TP401.1
unnamed: FB402.2, L402.1, TP402.1
unnamed: FB403.2, L403.1, TP403.1
unnamed: FB404.2, L404.1, TP404.1
unnamed: FB405.2, L405.1, TP405.1
unnamed: FB406.2, L406.1, TP406.1
unnamed: J501.2, R511.1
unnamed: J501.4, R512.1
unnamed: NT401.1, TL401.3
unnamed: NT402.1, TL402.3
unnamed: NT403.1, TL403.3
unnamed: Q301.1, R386.2
unnamed: Q302.1, R388.2, R389.1
unnamed: R105.2, R106.1
unnamed: R112.2, R113.1
unnamed: R114.2, R115.1
unnamed: R115.2, R116.1
unnamed: R207.2, R209.1, TP203.1, U201.1
unnamed: R210.2, R211.1, TP204.1, U202.1
unnamed: C103.1, R108.2, R109.1, TP101.1, U101.15
unnamed: C104.1, R110.1, R111.1, TP102.1, U101.14
unnamed: R104.2, R105.1, U101.2
unnamed: R106.2, U101.3
unnamed: R107.1, U101.7
unnamed: R207.1, R208.1, U201.4
unnamed: R209.2, R210.1, U202.4
unnamed: C308.2, U303.2
unnamed: C311.1, FB301.1, U303.7
unnamed: R315.2, R316.2, U305.1
unnamed: R319.2, R320.2, U305.3
unnamed: R323.2, R324.2, U306.1
unnamed: R327.2, R328.2, U306.3
unnamed: R331.2, R332.2, U307.1
unnamed: R335.2, R336.2, U307.3
unnamed: R339.2, R340.2, U308.1
unnamed: R343.2, R344.2, U308.3
unnamed: R347.2, R348.2, U309.1
unnamed: R351.2, R352.2, U309.3
unnamed: R355.2, R356.2, U310.1
unnamed: R359.2, R360.2, U310.3
unnamed: R363.2, R364.2, U311.1
unnamed: R367.2, R368.2, U311.3
unnamed: R371.2, R372.2, U312.1
unnamed: R375.2, R376.2, U312.3
unnamed: R311.2, U313.1
unnamed: R312.2, U313.2
unnamed: C401.2, U401.2
unnamed: C405.1, FB401.1, U401.7
unnamed: C406.2, U402.2
unnamed: C410.1, FB402.1, U402.7
unnamed: C412.2, U403.2
unnamed: C416.1, FB403.1, U403.7
unnamed: C417.2, U404.1
unnamed: C421.1, FB404.1, U404.3
unnamed: C422.2, U405.2
unnamed: C426.1, FB405.1, U405.7
unnamed: C427.2, U406.1
unnamed: C431.1, FB406.1, U406.3
unnamed: R508.1, U502.10
unnamed: R509.1, U502.9
unnamed: R510.1, U502.6
unnamed: U502.2, Y501.3
unnamed: U502.3, Y501.1
unnamed: C631.2, R609.2, R610.1, U601.5
unnamed: L602.1, U601.2
unnamed: R611.2, R612.1, U602.5
unnamed: L603.1, U602.2
unnamed: R603.2, R604.1, U603.4
unnamed: L601.1, U603.9
unnamed: L601.2, U603.7
unnamed: C618.1, U604.10
unnamed: C618.2, U604.9
unnamed: C626.1, U604.5
unnamed: R613.1, R614.2, U604.2
unnamed: R605.2, R606.1, U604.7
unnamed: C624.1, U605.10
unnamed: C624.2, U605.9
unnamed: C619.1, U605.5
unnamed: R615.1, R616.2, U605.2
unnamed: R607.2, R608.1, U605.7
unnamed: C722.1, R731.2, R732.1, U701.4
VBUS: C601.1, C602.1, C603.1, FB601.2, J501.1, R618.1, R619.1, R620.1, R621.1, U601.3, U601.4, U603.1, U603.2, U603.10, U608.5

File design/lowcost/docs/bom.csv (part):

qty,refs,value,footprint,mpn,lcsc,jlc_class,lcsc_stock,jlc_stock,lcsc_price_near10,unit,line,first_order,source,status,note
23,D201 D202 D301 D302 D303 D304 D305 D306 D307 D308 D309 D310 D311 D312 D313 D314 D315 D316 D317 D318 D319 D320 D401,BAT15-04W,SOT-323_SC-70,BAT1504WH6327XTSA1,C5380972,extended,865,865,0.3655 @10,0.3655,8.406,8.406,LCSC C5380972 (23+),ok,"LCSC / JLC stock 865 (25 Nov 2026, was 1465 on 24 Nov) = 37 boards at 23 per board: buy ahead of the order"
5,U303 U401 U402 U403 U405,TRF37D73,WSON-8-1EP_2x2mm_P0.5mm_EP0.9x1.6mm,TRF37D73IDSGR,C2151367,extended,25,25,1.2537 @10,1.5012,7.506,7.506,LCSC C2151367 (5+),ok,LCSC / JLC stock 25 (25 Nov 2026) = 5 boards; Mouser 7.3k (prices.md): buy ahead or consign
1,U501,GW1NZ-LV1QN48C6/I5,QFN-48-1EP_6x6mm_P0.4mm_EP4.3x4.3mm,,C5799569,extended,637,637,5.6426 @10,6.6772,6.677,6.677,LCSC C5799569 (1+),ok,
2,U404 U406,GVA-84+,SOT-89-3,GVA-84+,C5445191,extended,99,99,3.1417 @10,2.9900,5.980,5.980,Mouser (prices.md),ok,
1,U101,BUF802IRGTR,VQFN-16-1EP_3x3mm_P0.5mm_EP1.68x1.68mm,BUF802IRGTR,C4370628,extended,50,146,5.2858 @10,5.8889,5.889,5.889,LCSC C4370628 (1+),ok,
1,J101,SIG_IN,SMA_Samtec_SMA-J-P-X-ST-EM1_EdgeMount,SMA-J-P-H-ST-EM1,C5199907,extended,947,982,4.6757 @10,5.3403,5.340,5.340,LCSC C5199907 (2+),ok,Samtec SMA-J-P-H-ST-EM1 = footprint SMA_Samtec_SMA-J-P-X-ST-EM1
1,J102,EXT_CLK,SMA_Samtec_SMA-J-P-X-ST-EM1_EdgeMount,SMA-J-P-H-ST-EM1,C5199907,extended,947,982,4.6757 @10,5.3403,5.340,5.340,LCSC C5199907 (2+),ok,Samtec SMA-J-P-H-ST-EM1 = footprint SMA_Samtec_SMA-J-P-X-ST-EM1
1,U302,TLV3801,WSON-8-1EP_2x2mm_P0.5mm_EP0.9x1.6mm,TLV3801DSGR,C3658765,extended,37,113,4.4901 @10,5.1300,5.130,5.130,Mouser (prices.md),ok,
1,U704,STM32G474CBT6,LQFP-48_7x7mm_P0.5mm,,C730123,extended,133,192,4.0719 @10,4.6296,4.630,4.630,LCSC C730123 (1+),ok,CET6 C730125 as 2nd choice
9,U305 U306 U307 U308 U309 U310 U311 U312 U313,COS3502,SOIC-8_3.9x4.9mm_P1.27mm,COS3502SR,C49304672,extended,3705,3709,0.3588 @5,0.3588,3.229,3.229,LCSC C49304672 (9+),ok,
2,U604 U605,LM27762DSSR,WSON-12-1EP_3x2mm_P0.5mm_EP1x2.65,LM27762DSSR,C473398,extended,36133,37671,0.8060 @10,0.9596,1.919,1.919,LCSC C473398 (2+),ok,
3,U201 U202 U701,TPH2501,SOT-23-5,TPH2501-TR,C126713,extended,6040,6042,0.4311 @5,0.4311,1.293,2.155,LCSC C126713 (5+),ok,
32,C314 C315 C316 C317 C318 C319 C320 C321 C322 C323 C324 C325 C326 C327 C328 C329 C330 C331 C332 C333 C334 C335 C336 C337 C338 C339 C340 C341 C342 C343 C344 C345,0.5p,C_0402_1005Metric,GJM1555C1HR50WB01D,C76912,extended,105700,121170,0.0346 @20,0.0346,1.107,1.107,LCSC C76912 (32+),ok,
1,U603,TPS63802DLAR,Texas_DLA0010A_VSON-HR-10_2x3mm_P0.5mm,TPS63802DLAR,C2845237,extended,10464,10799,0.8060 @10,0.9510,0.951,0.951,LCSC C2845237 (1+),ok,
1,U502,MS5351M,MSOP-10_3x3mm_P0.5mm,,C1509083,extended,122,122,0.7552 @10,0.9112,0.911,0.911,LCSC C1509083 (1+),ok,
1,U102,OPA197IDBVR,SOT-23-5,OPA197IDBVR,C221351,extended,72975,73503,0.6214 @10,0.7499,0.750,0.750,LCSC C221351 (1+),ok,
7,L402 L403 L404 L405 L406 L602 L603,1u,L_1008_2520Metric,DFE252012F-1R0M,C435392,extended,68030,68034,0.1016 @5,0.1016,0.711,0.711,LCSC C435392 (7+),ok,
4,C632 C633 C634 C635,47u,C_1206_3216Metric,CL31A476MPHNNNE,C96123,basic,133115,570318,0.1645 @5,0.1645,0.658,0.823,LCSC C96123 (5+),ok,
6,C601 C604 C605 C610 C611 C612,22u,C_0805_2012Metric,CL21A226MAQNNNE,C45783,basic,600600,4614113,0.1095 @20,0.1095,0.657,2.190,LCSC C45783 (20+),ok,
20,C111 C116 C402 C407 C413 C420 C423 C430 C503 C507 C510 C603 C609 C617 C621 C625 C626 C628 C630 C714,10u,C_0805_2012Metric,CL21A106KAYNNNE,C15850,basic,1755840,9232088,0.0314 @20,0.0314,0.628,0.628,LCSC C15850 (20+),ok,
2,U601 U602,TPS62A01ADRLR,SOT-563,TPS62A01ADRLR,C5181455,extended,10020,10375,0.1974 @5,0.1974,0.395,0.987,LCSC C5181455 (5+),ok,
2,L302 L401,47u,L_1210_3225Metric,LQH32CN470K23L,C701189,extended,5310,5310,0.1632 @5,0.1632,0.326,0.816,LCSC C701189 (5+),ok,
1,L601,0.47u,L_XR0420_4.4x4.2mm,FXL0420-R47-M,C167200,extended,10620,10621,0.2938 @5,0.2938,0.294,1.469,LCSC C167200 (5+),ok,FXL0420-R47-M = XR0420 land (a 2.2 / b 5.2 / c 2.5 mm); alt. XR0420-R47M C5307593 (low stock)
73,C108 C109 C110 C112 C113 C114 C115 C208 C209 C210 C305 C306 C307 C309 C310 C313 C346 C347 C348 C349 C350 C351 C352 C353 C354 C355 C357 C359 C401 C403 C405 C406 C408 C410 C411 C412 C414 C416 C417 C419 C421 C422 C424 C426 C427 C429 C431 C432 C433 C434 C435 C501 C502 C504 C505 C506 C508 C509 C602 C606 C613 C622 C629 C709 C710 C711 C712 C713 C718 C719 C720 C721 C722,100n,C_0402_1005Metric,CL05B104KO5NNNC,C1525,basic,697500,31843434,0.0030 @100,0.0030,0.219,0.300,LCSC C1525 (100+),ok,
1,J601,USB-C 16P,USB_C_Receptacle_HRO_TYPE-C-31-M-12,HRO TYPE-C-31-M-12,C165948,extended,428795,441657,0.1888 @5,0.1888,0.189,0.944,LCSC C165948 (5+),ok,
9,FB301 FB401 FB402 FB403 FB404 FB405 FB406 FB608 FB701,1k,L_0402_1005Metric,BLM15HD102SN1D,C21516,extended,45250,61327,0.0197 @50,0.0197,0.177,0.985,LCSC C21516 (50+),ok,
1,U608,USBLC6-2SC6,SOT-23-6,,C7519,extended,43920,44027,0.1551 @5,0.1551,0.155,0.775,LCSC C7519 (5+),ok,may be left unfitted
1,T401,DLW21SN900HQ2L,L_CommonModeChoke_Coilcraft_0805USB,DLW21SN900HQ2L,C97855,extended,18825,19092,0.1479 @5,0.1479,0.148,0.740,LCSC C97855 (5+),ok,
7,FB601 FB602 FB603 FB604 FB605 FB606 FB607,120R@100MHz,L_0603_1608Metric,BLM18PG121SN1D,C14709,basic,1705350,2332391,0.0151 @50,0.0151,0.106,0.755,LCSC C14709 (50+),ok,
1,Y501,25MHz,Crystal_SMD_3225-4Pin_3.2x2.5mm,,C9006,basic,187715,343073,0.0915 @5,0.0915,0.091,0.458,LCSC C9006 (5+),ok,
15,C103 C104 C308 C311 C312 C356 C358 C607 C608 C615 C623 C624 C627 C715 C717,1u,C_0402_1005Metric,CL05A105KA5NQNC,C52923,basic,3628700,12661100,0.0056 @100,0.0056,0.084,0.560,LCSC C52923 (100+),ok,
53,R108 R110 R121 R204 R205 R206 R207 R209 R210 R315 R316 R319 R320 R323 R324 R327 R328 R331 R332 R335 R336 R339 R340 R343 R344 R347 R348 R351 R352 R355 R356 R359 R360 R363 R364 R367 R368 R371 R372 R375 R376 R380 R381 R382 R387 R390 R391 R392 R393 R394 R415 R724 R730,1k,R_0402_1005Metric,0402WGF1001TCE,C11702,basic,14799500,28492968,0.0011 @100,0.0011,0.058,0.110,LCSC C11702 (100+),ok,
1,C101,1.5p,C_0402_1005Metric,GJM1555C1H1R5WB01D,C76901,extended,17500,17507,0.0428 @20,0.0428,0.043,0.856,LCSC C76901 (20+),ok,
4,R618 R619 R620 R621,1,R_1206_3216Metric,1206W4F100KT5E,C17928,basic,0,154940,0.0103 @50,0.0103,0.041,0.515,LCSC C17928 (50+),ok,
33,R313 R314 R317 R318 R321 R322 R325 R326 R329 R330 R333 R334 R337 R338 R341 R342 R345 R346 R349 R350 R353 R354 R357 R358 R361 R362 R365 R366 R369 R370 R373 R374 R604,2.2k,R_0402_1005Metric,0402WGF2201TCE,C25879,basic,823200,2640606,0.0012 @100,0.0012,0.040,0.120,LCSC C25879 (100+),ok,
1,C102,3.3p,C_0402_1005Metric,GJM1555C1H3R3BB01D,C76906,extended,169450,174961,0.0277 @50,0.0277,0.028,1.385,LCSC C76906 (50+),ok,
7,C203 C204 C206 C304 C614 C702 C716,10n,C_0402_1005Metric,CL05B103KB5NNNC,C15195,basic,1484400,5923466,0.0038 @100,0.0038,0.027,0.380,LCSC C15195 (100+),ok,
5,R385 R389 R704 R734 R737,3.3k,R_0402_1005Metric,0402WGF3301TCE,C25890,basic,402100,1415362,0.0036 @100,0.0036,0.018,0.360,LCSC C25890 (100+),ok,
11,R118 R501 R502 R503 R504 R505 R506 R507 R727 R728 R735,4.7k,R_0402_1005Metric,0402WGF4701TCE,C25900,basic,4314100,12570656,0.0016 @100,0.0016,0.018,0.160,LCSC C25900 (100+),ok,
1,C619,4.7u,C_0603_1608Metric,CL10A475KO8NNNC,C19666,basic,0,3012885,0.0171 @10,0.0171,0.017,0.171,LCSC C19666 (10+),ok,
2,C616 C620,4.7u,C_0402_1005Metric,CL05A475MP5NRNC,C23733,basic,2210000,2961761,0.0082 @50,0.0082,0.016,0.410,LCSC C23733 (50+),ok,
1,Q301,SS8550,SOT-23,SS8550 Y2,C8542,basic,494550,883904,0.0149 @50,0.0149,0.015,0.745,LCSC C8542 (50+),ok,
1,C618,1u,C_0603_1608Metric,CL10A105KB8NNNC,C15849,basic,250,11744059,0.0142 @50,0.0142,0.014,0.710,LCSC C15849 (50+),ok,
11,R112 R301 R310 R377 R378 R379 R401 R405 R406 R407 R411,49.9,R_0402_1005Metric,0402WGF499JTCE,C25120,basic,185100,1106467,0.0012 @100,0.0012,0.013,0.120,LCSC C25120 (100+),ok,
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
